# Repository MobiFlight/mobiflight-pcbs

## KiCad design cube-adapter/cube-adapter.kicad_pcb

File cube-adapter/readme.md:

# MobiFlight Cube Adapter
The MobiFlight Cube Adapter is a breakout board to learn and experiment with the different input and output devices that are supported by MobiFlight.
The board uses XH JST connectors of different sizes depending on the type of device. These connectors ensure a secure connection and correct orientation of the plugs.

## Devices overview

### Button 1 - 6
Simple buttons that connect with just two wires.

Left pin is Ground, right pin is VCC.

### LEDs 1 - 6
All LEDs are using PWM enabled pins and can be dimmed in MobiFlight.
It is recommended to add a apropriate resistor for you LED. 
More information: https://github.com/MobiFlight/MobiFlight-Connector/wiki/Input-and-Output-devices#led--output

Left pin is Ground, right pin is VCC.

### Switch 1 - 5 (On-On)
Connector is designed for On-On switches or two position switches.
More information: https://github.com/MobiFlight/MobiFlight-Connector/wiki/Input-and-Output-devices#buttons-and-switches

Left pin is Button 1, middle pin is GND, right pin is Button 2.

### Switch 6 - 10 (On-Off-On)
Connector is designed for On-Off-On switches or three position switches.
More information: https://github.com/MobiFlight/MobiFlight-Connector/wiki/Input-and-Output-devices#buttons-and-switches

* Left pin is Button 1,
* middle pin is GND, 
* right pin is Button 2.

### 7-Segment 1
Connect a 7219MAX-chip based board to this pin.
More information: https://github.com/MobiFlight/MobiFlight-Connector/wiki/Input-and-Output-devices#7-segment-modules

* 1st pin GND,
* 2nd pin VCC,
* 3rd pin DIN,
* 4th pin CS,
* 5th pin CLK

### Encoder 1-3
Connect a Encoder with Push Button function.
More information: https://github.com/MobiFlight/MobiFlight-Connector/wiki/Input-and-Output-devices#encoders

* 1st pin GND
* 2nd pin Left Pin (A)
* 3rd pin Right Pin (B)
* 4th pin Push Button

### Pot 1 - 3
Connect a Potentiometer or other analog input device.
More information: https://github.com/MobiFlight/MobiFlight-Connector/wiki/Input-and-Output-devices#analog-inputs

* 1st pin GND
* 2nd pin Reading
* 3rd pin VCC

### Shift-Register 1-2
Connect an output shift register.
More information: https://github.com/MobiFlight/MobiFlight-Connector/wiki/Input-and-Output-devices#output-shift-registers

* 1st pin GND
* 2nd pin VCC
* 3rd pin SPI (Latch)
* 4th pin SPI (Clock)
* 5th pin SPI (Data)

### Servo 1-2
Connect a servo. More information: https://github.com/MobiFlight/MobiFlight-Connector/wiki/Input-and-Output-devices#servos-motors

### Stepper 1-2
Connect a stepper. More information: https://github.com/MobiFlight/MobiFlight-Connector/wiki/Input-and-Output-devices#stepper-motors

### LCD Display 1-2
Connect a LCD Display. More information: https://github.com/MobiFlight/MobiFlight-Connector/wiki/Input-and-Output-devices#lcd-displays

* 1st pin GND
* 2nd pin VCC
* 3rd pin I2C - SDA
* 4th pin I2C - SCL

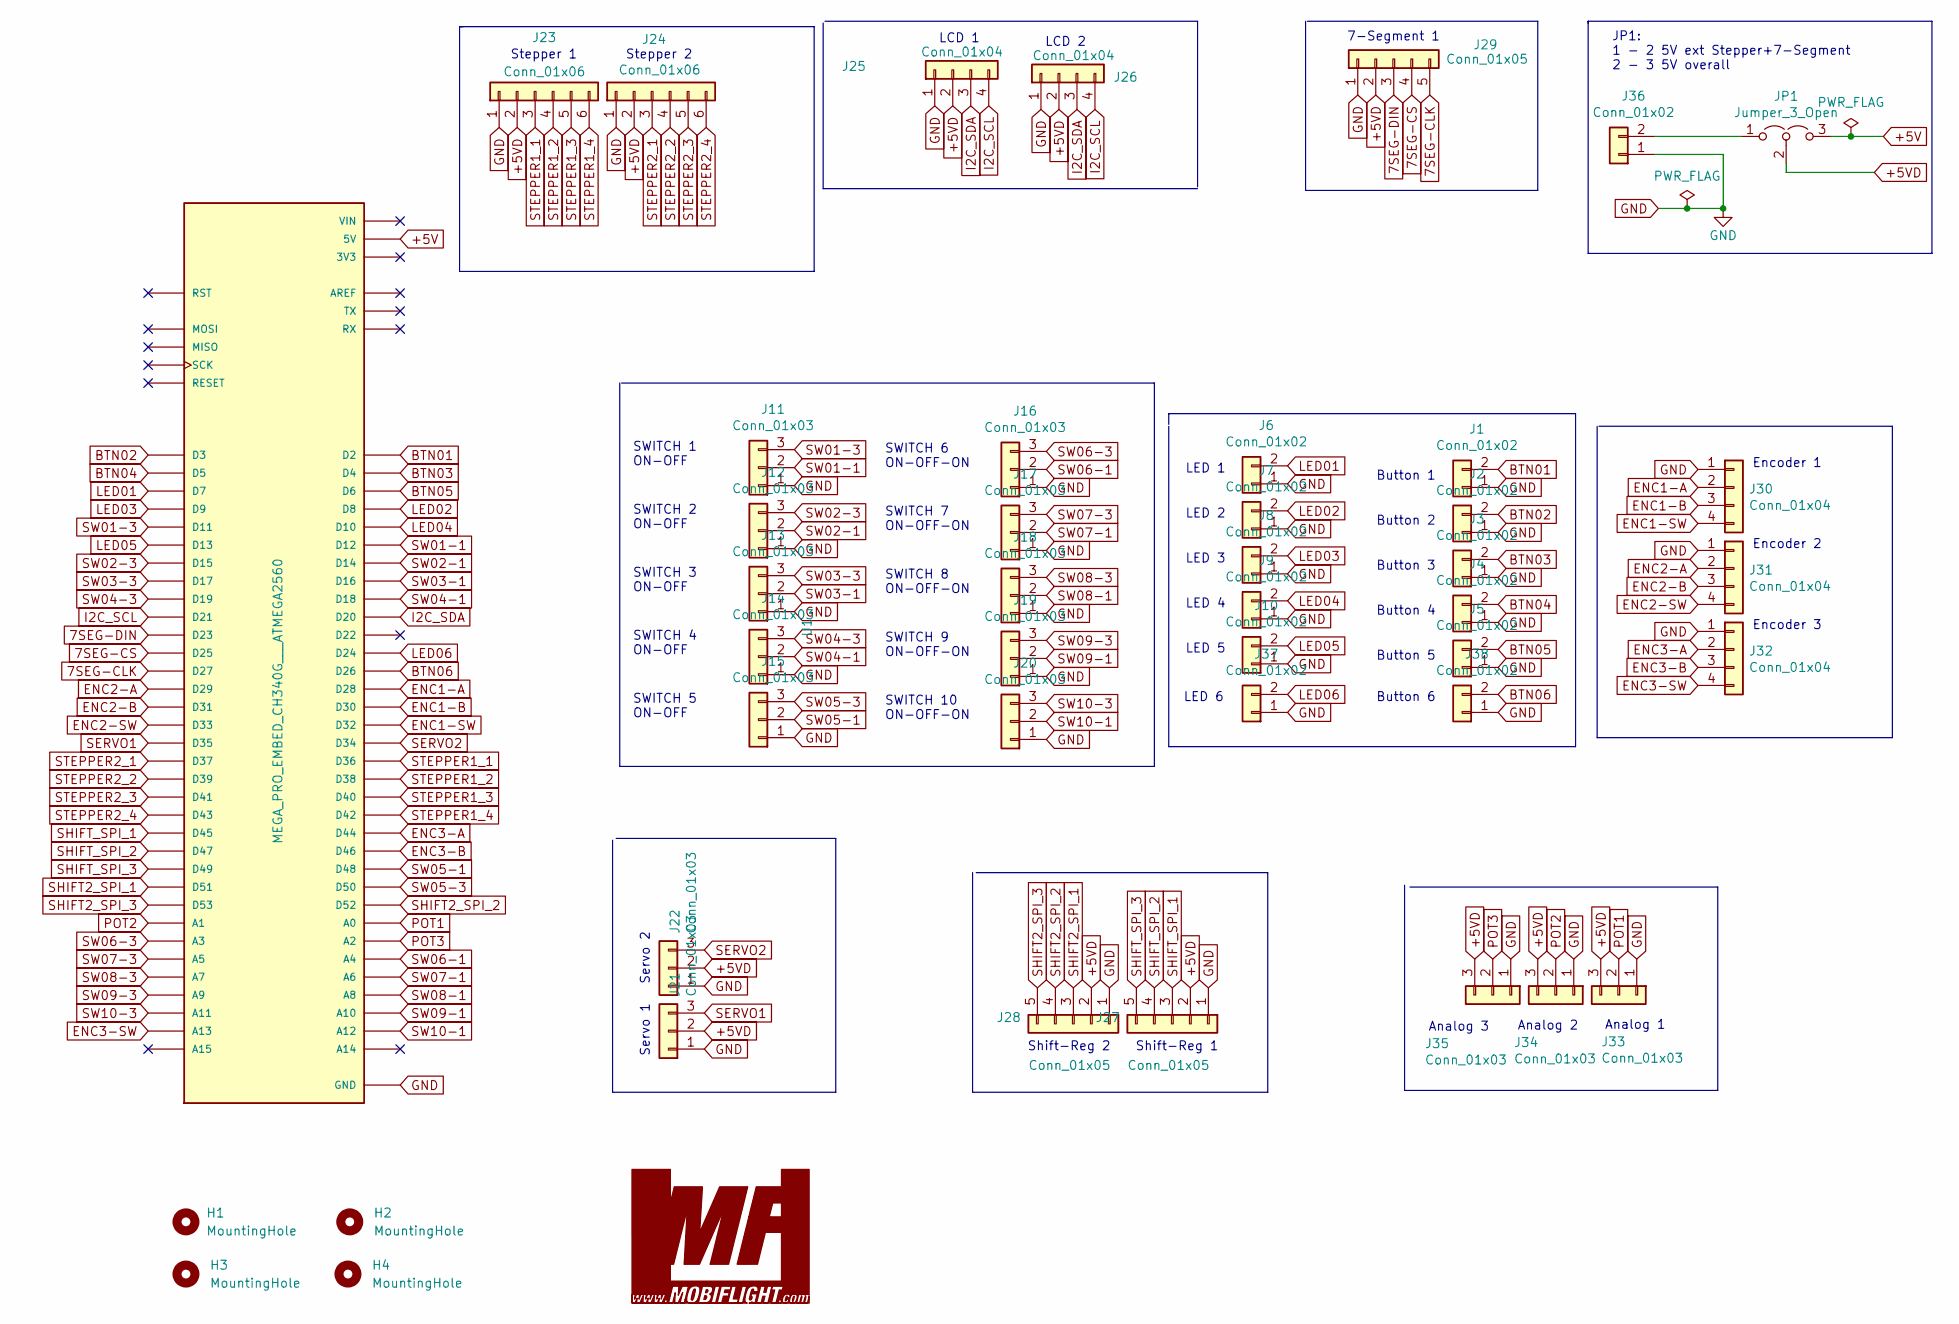
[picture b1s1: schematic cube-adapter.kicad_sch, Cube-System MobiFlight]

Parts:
H1, H2, H3, H4: MountingHole; MountingHole_3.5mm
J1, J2, J3, J4, J5, J6, J7, J8, J9, J10, J36, J37, J38: Conn_01x02; JST_XH_B2B-XH-A_1x02_P2.50mm_Vertical
J11, J12, J13, J14, J15, J16, J17, J18, J19, J20, J21, J22, J33, J34, J35: Conn_01x03; JST_XH_B3B-XH-A_1x03_P2.50mm_Vertical
J23, J24: Conn_01x06; JST_XH_B6B-XH-A_1x06_P2.50mm_Vertical
J25, J26, J30, J31, J32: Conn_01x04; JST_XH_B4B-XH-A_1x04_P2.50mm_Vertical
J27, J28, J29: Conn_01x05; JST_XH_B5B-XH-A_1x05_P2.50mm_Vertical
JP1: Jumper_3_Open; PinHeader_1x03_P2.54mm_Vertical
U1: MEGA_PRO_EMBED_CH340G___ATMEGA2560; _ATMEGA2560; PARTREV 12/May/2017

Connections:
7SEG-CLK: J29.5, U1.D27
7SEG-CS: J29.4, U1.D25
7SEG-DIN: J29.3, U1.D23
+5V: JP1.3 (B), U1.5V_1 (5V), U1.5V_2 (5V), U1.5V_3 (5V)
+5VD: J21.2, J22.2, J23.2, J24.2, J25.2, J26.2, J27.2, J28.2, J29.2, J33.3, J34.3, J35.3, JP1.2 (C)
BTN01: J1.2, U1.D2
BTN02: J2.2, U1.D3
BTN03: J3.2, U1.D4
BTN04: J4.2, U1.D5
BTN05: J5.2, U1.D6
BTN06: J38.2, U1.D26
ENC1-A: J30.2, U1.D28
ENC1-B: J30.3, U1.D30
ENC1-SW: J30.4, U1.D32
ENC2-A: J31.2, U1.D29
ENC2-B: J31.3, U1.D31
ENC2-SW: J31.4, U1.D33
ENC3-A: J32.2, U1.D44
ENC3-B: J32.3, U1.D46
ENC3-SW: J32.4, U1.A13
GND: J1.1, J2.1, J3.1, J4.1, J5.1, J6.1, J7.1, J8.1, J9.1, J10.1, J11.1, J12.1, J13.1, J14.1, J15.1, J16.1, J17.1, J18.1, J19.1, J20.1, J21.1, J22.1, J23.1, J24.1, J25.1, J26.1, J27.1, J28.1, J29.1, J30.1, J31.1, J32.1, J33.1, J34.1, J35.1, J36.1, J37.1, J38.1, U1.GND_1 (GND), U1.GND_2 (GND), U1.GND_3 (GND)
I2C_SCL: J25.4, J26.4, U1.D21
I2C_SDA: J25.3, J26.3, U1.D20
LED01: J6.2, U1.D7
LED02: J7.2, U1.D8
LED03: J8.2, U1.D9
LED04: J9.2, U1.D10
LED05: J10.2, U1.D13
LED06: J37.2, U1.D24
unnamed: J36.2, JP1.1 (A)
POT1: J33.2, U1.A0
POT2: J34.2, U1.A1
POT3: J35.2, U1.A2
SERVO1: J21.3, U1.D35
SERVO2: J22.3, U1.D34
SHIFT2_SPI_1: J28.3, U1.D51
SHIFT2_SPI_2: J28.4, U1.D52
SHIFT2_SPI_3: J28.5, U1.D53
SHIFT_SPI_1: J27.3, U1.D45
SHIFT_SPI_2: J27.4, U1.D47
SHIFT_SPI_3: J27.5, U1.D49
STEPPER1_1: J23.3, U1.D36
STEPPER1_2: J23.4, U1.D38
STEPPER1_3: J23.5, U1.D40
STEPPER1_4: J23.6, U1.D42
STEPPER2_1: J24.3, U1.D37
STEPPER2_2: J24.4, U1.D39
STEPPER2_3: J24.5, U1.D41
STEPPER2_4: J24.6, U1.D43
SW01-1: J11.2, U1.D12
SW01-3: J11.3, U1.D11
SW02-1: J12.2, U1.D14
SW02-3: J12.3, U1.D15
SW03-1: J13.2, U1.D16
SW03-3: J13.3, U1.D17
SW04-1: J14.2, U1.D18
SW04-3: J14.3, U1.D19
SW05-1: J15.2, U1.D48
SW05-3: J15.3, U1.D50
SW06-1: J16.2, U1.A4
SW06-3: J16.3, U1.A3
SW07-1: J17.2, U1.A6
SW07-3: J17.3, U1.A5
SW08-1: J18.2, U1.A8
SW08-3: J18.3, U1.A7
SW09-1: J19.2, U1.A10
SW09-3: J19.3, U1.A9
SW10-1: J20.2, U1.A12
SW10-3: J20.3, U1.A11

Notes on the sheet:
SWITCH 6 ON-OFF-ON
Button 6
Servo 1
Analog 3
LCD 2
LED 5
Shift-Reg 1
LED 4
SWITCH 4 ON-OFF
Encoder 3
Button 1
Analog 1
JP1: 1 - 2 5V ext Stepper+7-Segment 2 - 3 5V overall
SWITCH 9 ON-OFF-ON
7-Segment 1
Encoder 2
SWITCH 3 ON-OFF
Analog 2
Servo 2
Encoder 1
SWITCH 8 ON-OFF-ON
LED 1
Stepper 1
Button 3
SWITCH 2 ON-OFF
LED 2
SWITCH 10 ON-OFF-ON
Shift-Reg 2
LED 3
SWITCH 1 ON-OFF
LED 6
Button 5
Button 2
SWITCH 5 ON-OFF
Button 4
LCD 1
Stepper 2
SWITCH 7 ON-OFF-ON

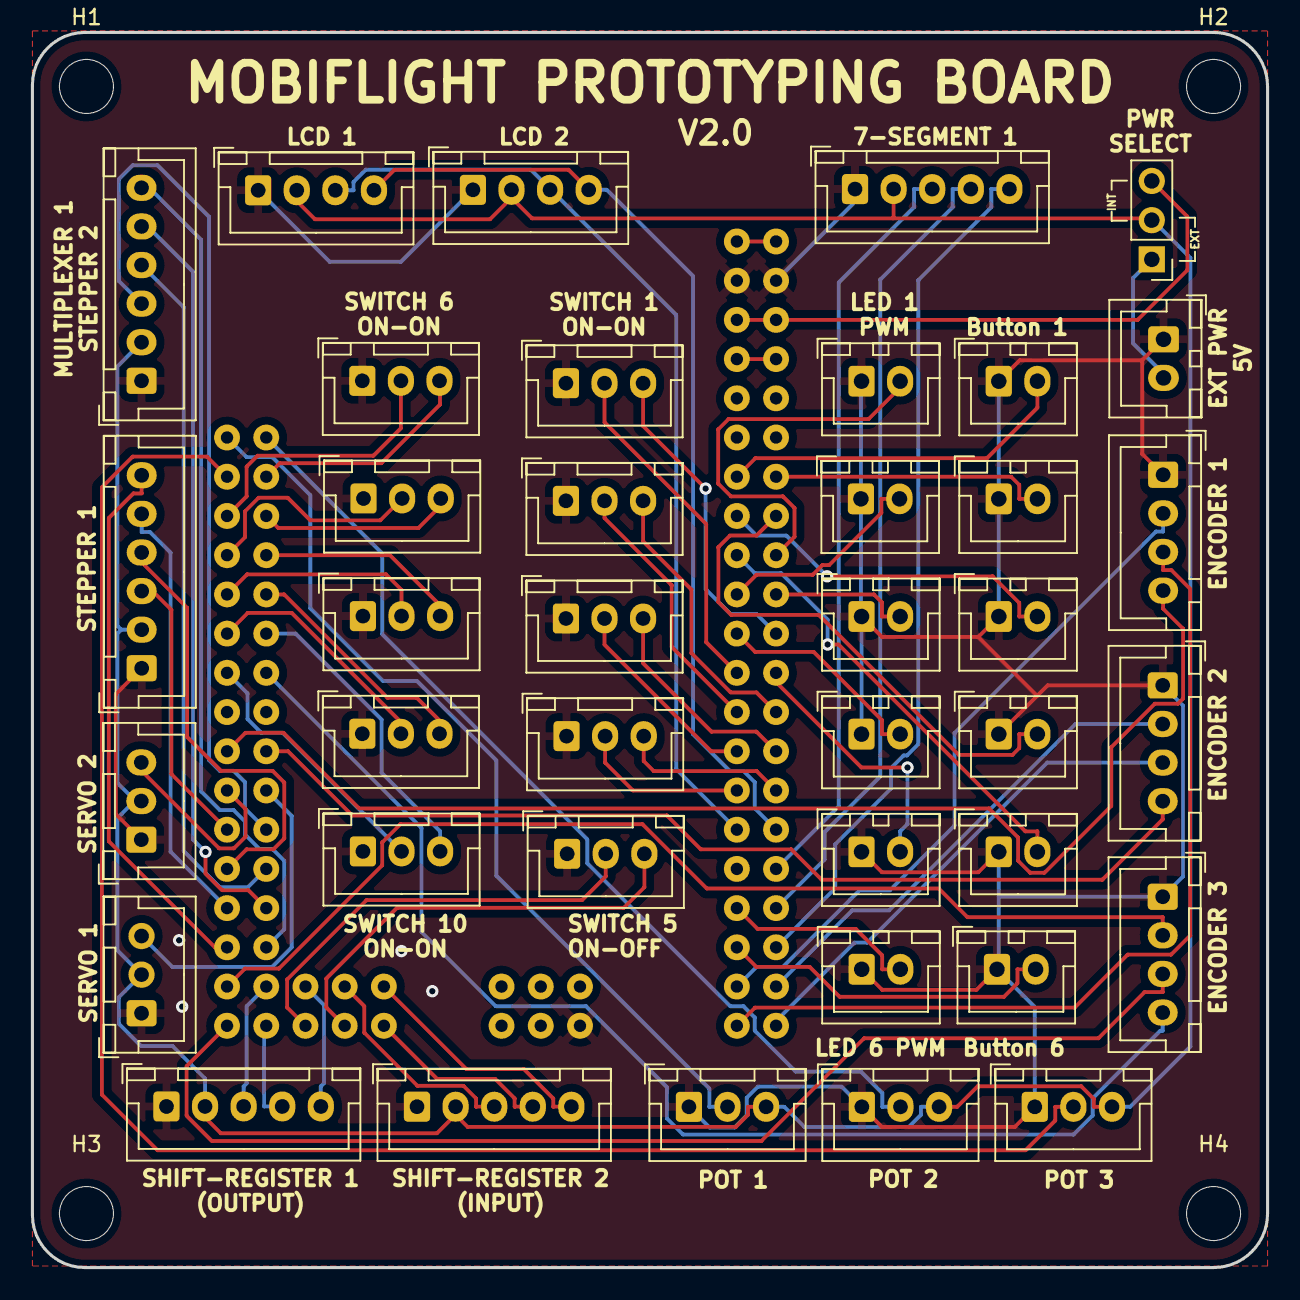
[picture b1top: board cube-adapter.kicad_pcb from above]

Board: 2 copper layers, 80.0 x 80.0 mm, 44 parts (1 on the bottom side), 69 nets.

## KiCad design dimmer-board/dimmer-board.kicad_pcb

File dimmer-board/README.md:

# Light dimmer board

This is a light dimmer board for backlight and cockpit lights, works as a shield on a full sized Arduino Mega, or standalone.

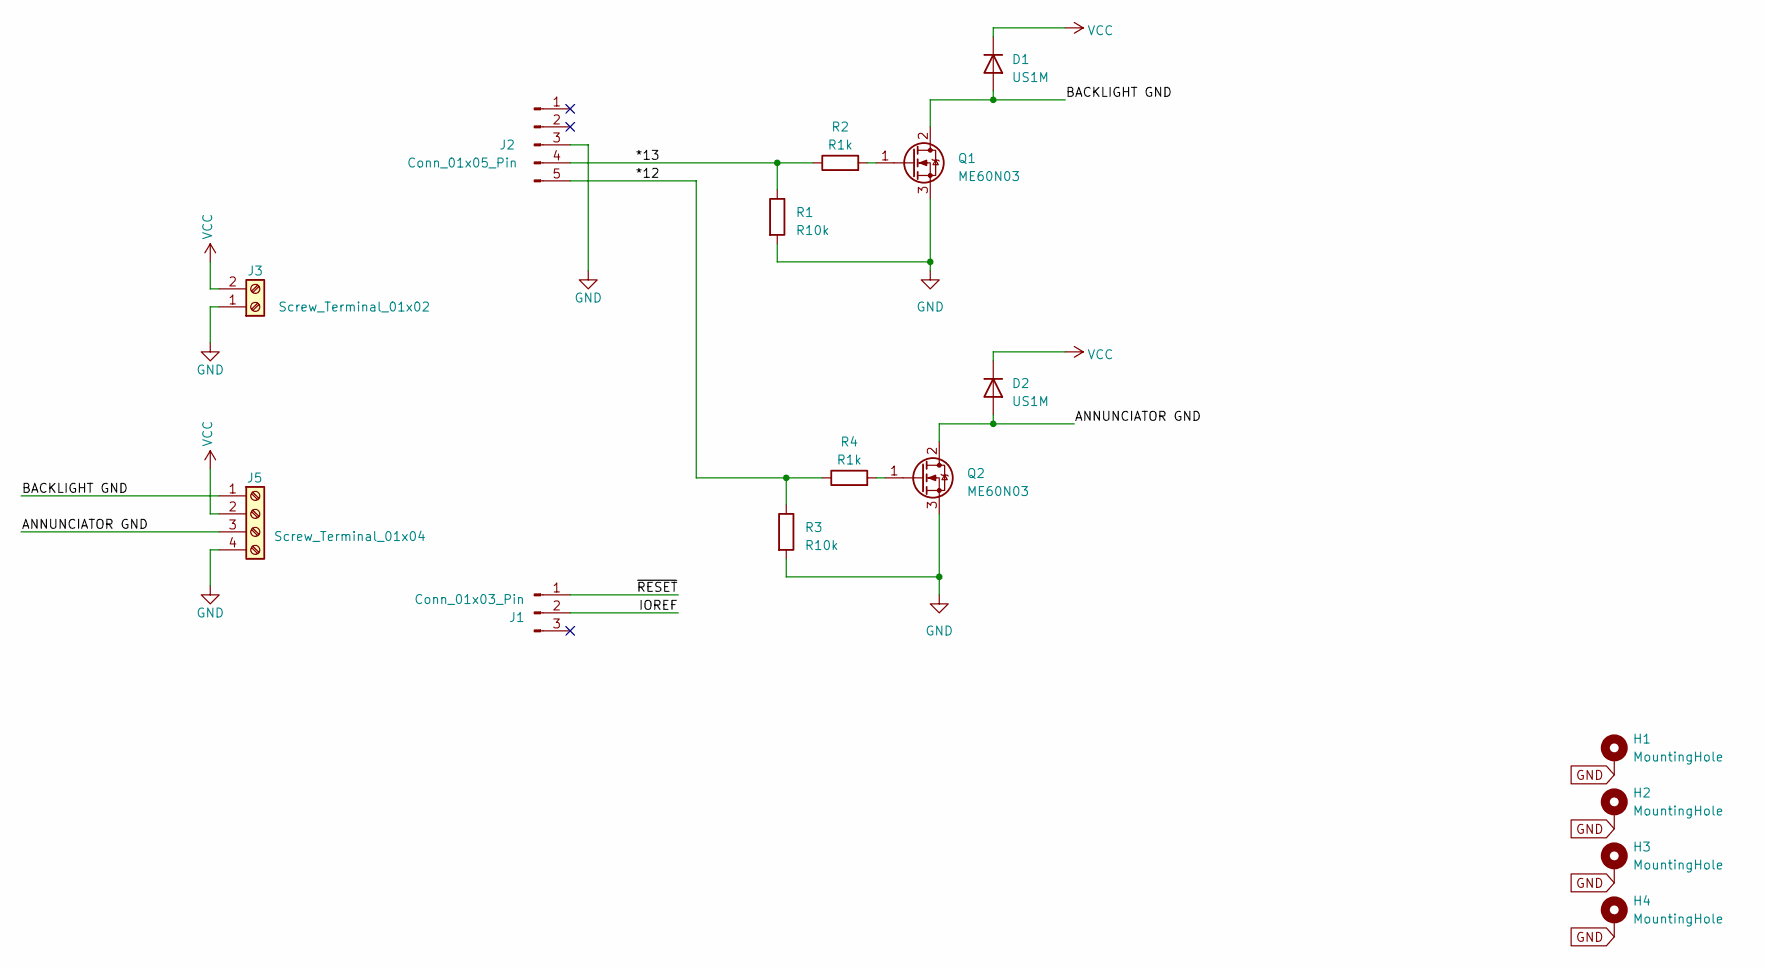
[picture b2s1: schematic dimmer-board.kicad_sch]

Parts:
D1, D2: US1M; D_SMA; LCSC C412437
H1, H2, H3, H4: MountingHole; MountingHole_3.2mm_M3_ISO14580_Pad_TopBottom
J1: Conn_01x03_Pin; PinHeader_1x03_P2.54mm_Vertical
J2: Conn_01x05_Pin; PinHeader_1x05_P2.54mm_Vertical
J3: Screw_Terminal_01x02; TerminalBlock_bornier-2_P5.08mm; LCSC C395882
J5: Screw_Terminal_01x04; TerminalBlock_bornier-4_P5.08mm; LCSC C3034542
Q1, Q2: ME60N03; TO-252-2; LCSC C165232
R1, R3: R10k; R_1206_3216Metric; LCSC C17902
R2, R4: R1k; R_1206_3216Metric; LCSC C4410

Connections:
/*12: J2.5, R3.1, R4.1
/*13: J2.4, R1.1, R2.1
/ANNUNCIATOR GND: D2.2 (A), J5.3, Q2.2 (D)
/BACKLIGHT GND: D1.2 (A), J5.1, Q1.2 (D)
/IOREF: J1.2
/~RESET: J1.1
GND: H1.1, H2.1, H3.1, H4.1, J2.3, J3.1, J5.4, Q1.3 (S), Q2.3 (S), R1.2, R3.2
unnamed: Q1.1 (G), R2.2
unnamed: Q2.1 (G), R4.2
VCC: D1.1 (K), D2.1 (K), J3.2, J5.2

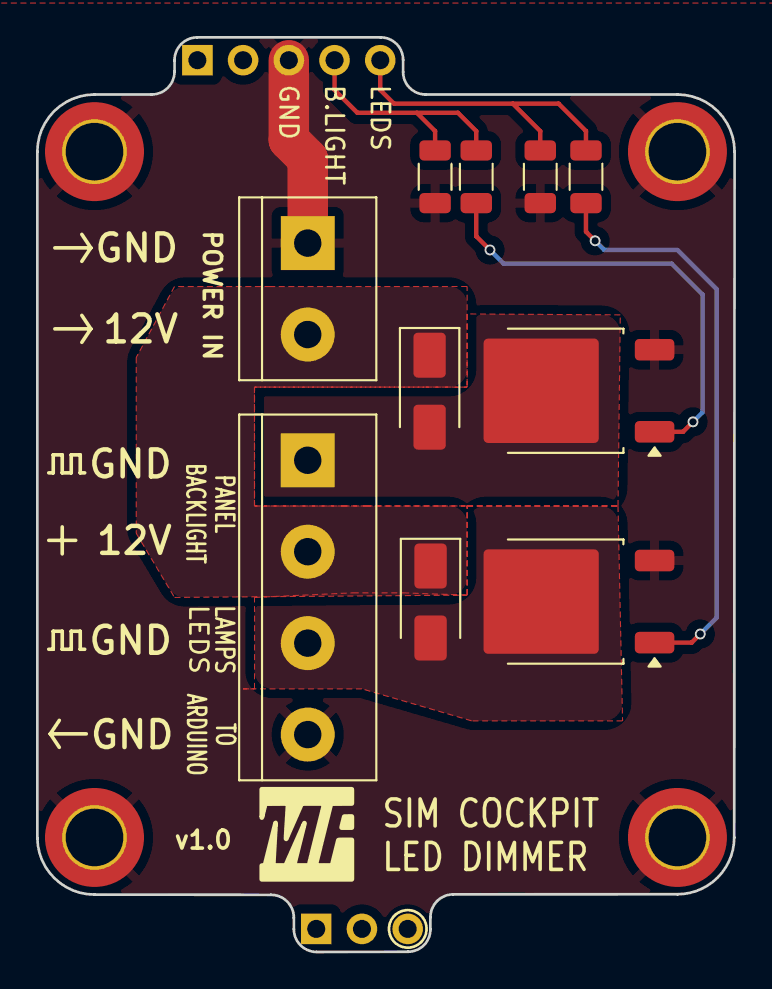
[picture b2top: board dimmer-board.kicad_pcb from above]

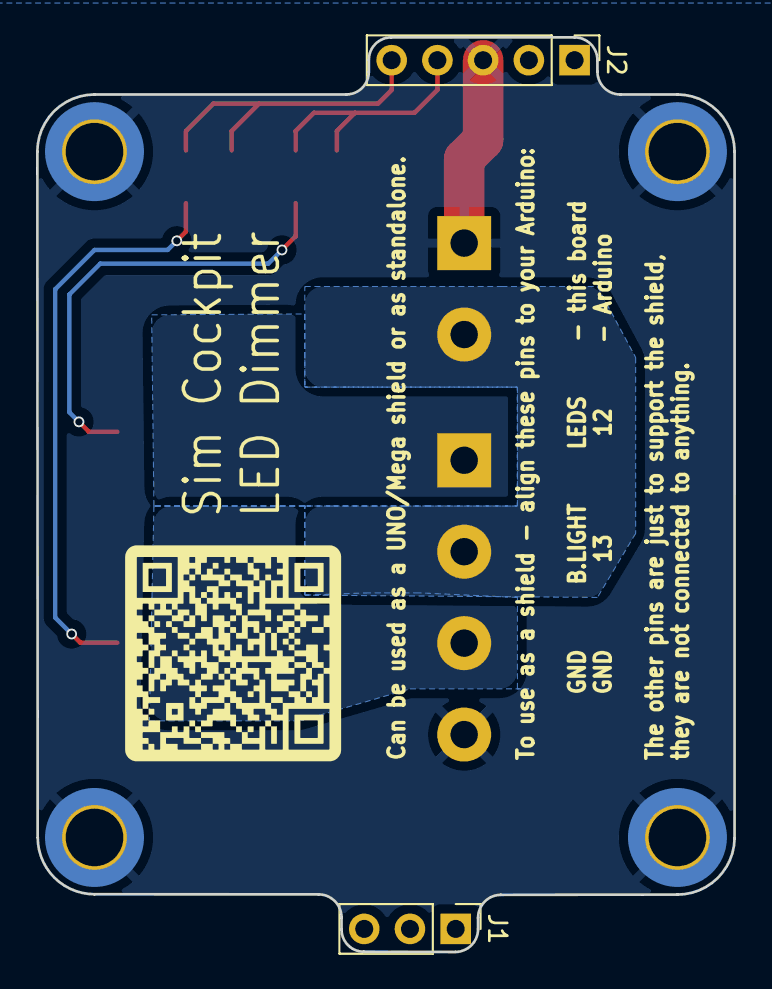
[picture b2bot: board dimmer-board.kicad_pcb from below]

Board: 2 copper layers, 38.7 x 50.8 mm, 16 parts (2 on the bottom side), 8 nets.

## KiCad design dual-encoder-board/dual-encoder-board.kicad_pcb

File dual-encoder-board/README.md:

# Dual encoder board

The dual encoder board was created because the commonly available and most affordable, and thus most popular 
dual encoder for cockpit building does not have threads on the shaft, and it is thus hard to mount on panels 
without using a printed circuit board.

The encoder board features a soldering footprint for the encoder as well as two JST XH connectors that let you
attach the encoder for example to a [MobiFlight Cube adapter](https://github.com/MobiFlight/mobiflight-pcbs/tree/main/cube-adapter) 
with a 4 pin JST XH cable.

The board has a 20x20mm pattern of M3 mounting holes, so you can use nylon standoffs and M3 machine screws to attach it
to an acrylic panel for example. The encoder body is about 7mm tall, so 8mm standoffs work great.

This repository contains the KiCad project files and also a gerber zip that can be used to manufacture the board.
But if you are interested in this board, you can also find it in the 
[MobiFlight Community Shop](https://shop.mobiflight.com/product/dual-encoder-bundle) bundled with a resin printed
knob set. I recreated the board while learning to use KiCad, so this is slightly different in how it looks,
but it will replace the older stock in the shop once that runs out. 

Both variants are functionally identical.

Designed by Tuomas Kuosmanen, November 2022

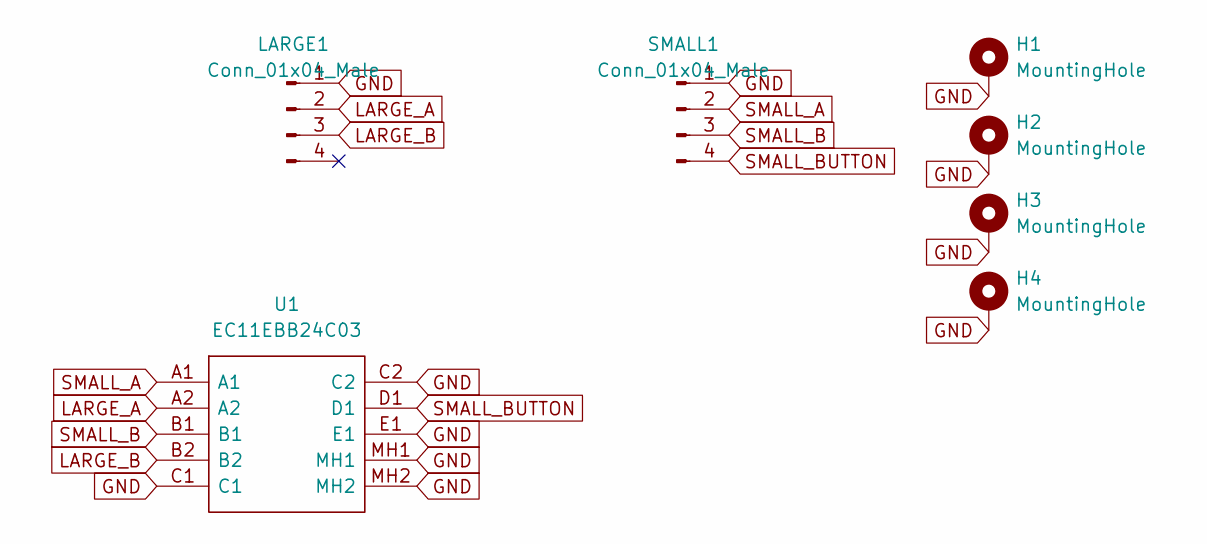
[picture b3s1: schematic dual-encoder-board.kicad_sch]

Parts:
H1, H2, H3, H4: MountingHole; MountingHole_3.2mm_M3_ISO14580_Pad_TopBottom
LARGE1: Conn_01x04_Male; JST_XH_B4B-XH-A_1x04_P2.50mm_Vertical
SMALL1: Conn_01x04_Male; JST_XH_B4B-XH-A_1x04_P2.50mm_Vertical
U1: EC11EBB24C03; EC11EBB24C03_oval; Manufacturer_Part_Number EC11EBB24C03; Mouser Part Number 688-EC11EBB24C03

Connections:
GND: H1.1, H2.1, H3.1, H4.1, LARGE1.1, SMALL1.1, U1.C1, U1.C2, U1.E1, U1.MH1, U1.MH2
LARGE_A: LARGE1.2, U1.A2
LARGE_B: LARGE1.3, U1.B2
SMALL_A: SMALL1.2, U1.A1
SMALL_B: SMALL1.3, U1.B1
SMALL_BUTTON: SMALL1.4, U1.D1

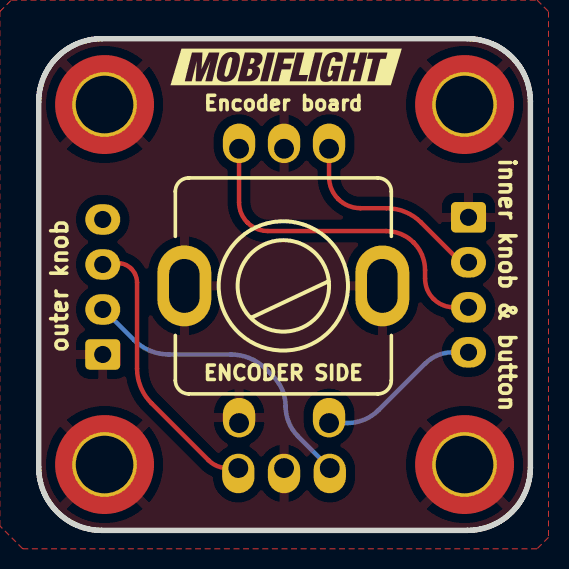
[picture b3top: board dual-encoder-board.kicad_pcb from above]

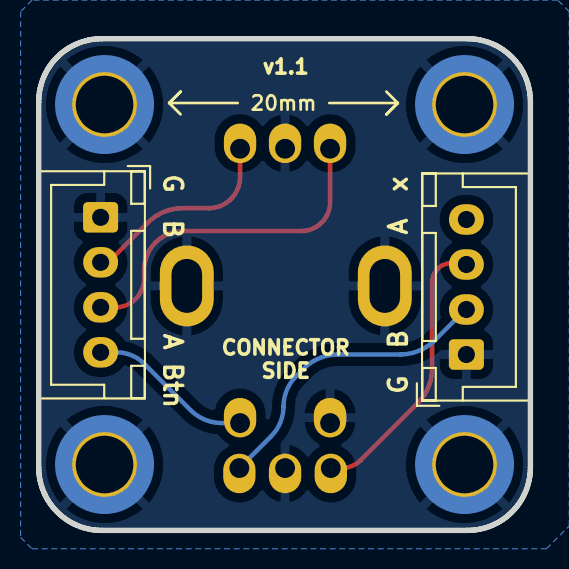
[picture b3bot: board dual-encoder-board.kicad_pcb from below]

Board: 2 copper layers, 27.3 x 27.3 mm, 8 parts (2 on the bottom side), 6 nets.

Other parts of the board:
kibuzzard-6380ACF0: G***; kibuzzard-6380ACF0

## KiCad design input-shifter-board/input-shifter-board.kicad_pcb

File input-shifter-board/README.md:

# MobiFlight Input Shifter Board
The MobiFlight Input Shifter Board is a breakout board for easier use of up to 32 buttons. It is designed to work best together with the [MobiFlight Prototyping Board](https://shop.mobiflight.com/product/prototyping-board-v2).

The board uses XH JST connectors for the individual buttons and for connecting to the Prototyping Board. Four 8 bit input shift register are daisy chained. Each input has a LED beside the connector which indicates if the button is pressed.

For more information on how to configure the board with MobiFlight, check out the [MobiFlight Connector documentation](https://docs.mobiflight.com/devices/input-shift-register/).

## Board overview

### Input Shifter IN
Connection coming from your Mobiflight board.

* Pin1 - GND
* Pin2 - VCC
* Pin3 - Latch
* Pin4 - Clock
* Pin5 - Data

### Button 1-32
Connect your button to these connectors.

Polarity does not matter for Buttons.

## Connecting and wiring
The Input Shifter board is designed to work best together with the [MobiFlight Prototyping Board](https://shop.mobiflight.com/product/prototyping-board-v2). Of course, you can also connect it directly to any of the supported microcontrollers.

### MobiFlight Prototyping Board
The prototyping board comes with the required cables to make connection super easy.

* **Connect the 5-pin wire** from the breakout board to the MobiFlight Prototyping Board's 5-pin connector labeled **Shift-Register 2**
* **Upload input shifter board configuration** to the MobiFlight Prototyping Board - [Download multiplexer-config (mfmc)](https://raw.githubusercontent.com/MobiFlight/mobiflight-pcbs/refs/heads/main/led-driver-board/prototyping-board.input-shifter.mfmc)

All inputs on the Input shifter will now work correctly!

### Direct connection
If you are using any of the supported microcontrollers, do the following:

#### Wiring
* Connect the first two pins on the **Data In** connector to **GND**, **5V** and the three remaining pins to free output-capable pins. For an Arduino Mega that could be, eg. D2, D3 D4 and D5. 

#### Board configuration
Add one input shifter device with the three data pins configured as follows and choose four times 8 bit.

Click "Upload config" and your device should work.

## MobiFlight Configuration

> This information will be added soon.

## Case
You can print a case for the board [using this STL file](breakout-multiplexer-case.stl) for better handling and look:

## Additional information

### Bottom side

### Schematic

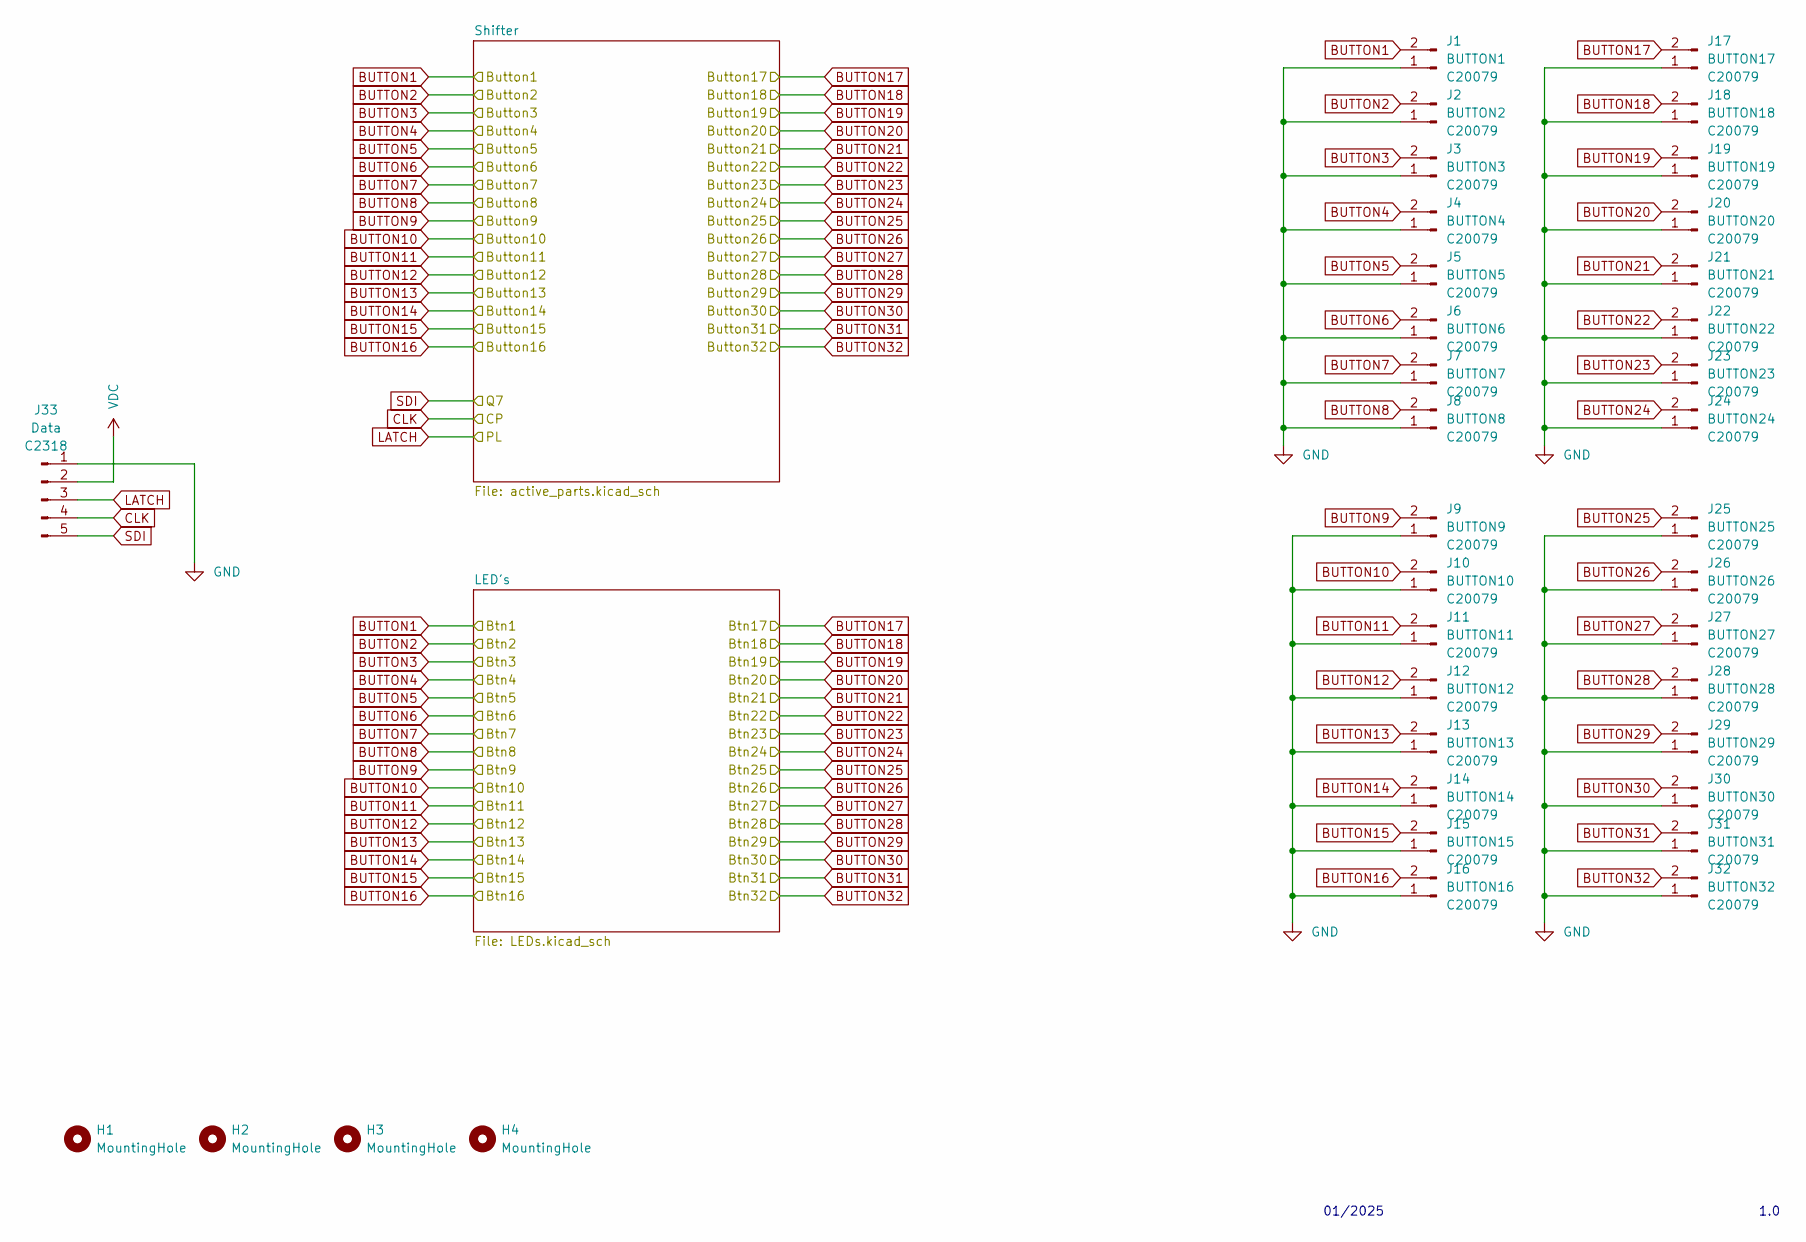
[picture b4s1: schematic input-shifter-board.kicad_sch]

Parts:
H1, H2, H3, H4: MountingHole; MountingHole_3.2mm_M3_Pad
J1: BUTTON1; JST_XH_B2B-XH-A_1x02_P2.50mm_Vertical; LCSC C20079
J2: BUTTON2; JST_XH_B2B-XH-A_1x02_P2.50mm_Vertical; LCSC C20079
J3: BUTTON3; JST_XH_B2B-XH-A_1x02_P2.50mm_Vertical; LCSC C20079
J4: BUTTON4; JST_XH_B2B-XH-A_1x02_P2.50mm_Vertical; LCSC C20079
J5: BUTTON5; JST_XH_B2B-XH-A_1x02_P2.50mm_Vertical; LCSC C20079
J6: BUTTON6; JST_XH_B2B-XH-A_1x02_P2.50mm_Vertical; LCSC C20079
J7: BUTTON7; JST_XH_B2B-XH-A_1x02_P2.50mm_Vertical; LCSC C20079
J8: BUTTON8; JST_XH_B2B-XH-A_1x02_P2.50mm_Vertical; LCSC C20079
J9: BUTTON9; JST_XH_B2B-XH-A_1x02_P2.50mm_Vertical; LCSC C20079
J10: BUTTON10; JST_XH_B2B-XH-A_1x02_P2.50mm_Vertical; LCSC C20079
J11: BUTTON11; JST_XH_B2B-XH-A_1x02_P2.50mm_Vertical; LCSC C20079
J12: BUTTON12; JST_XH_B2B-XH-A_1x02_P2.50mm_Vertical; LCSC C20079
J13: BUTTON13; JST_XH_B2B-XH-A_1x02_P2.50mm_Vertical; LCSC C20079
J14: BUTTON14; JST_XH_B2B-XH-A_1x02_P2.50mm_Vertical; LCSC C20079
J15: BUTTON15; JST_XH_B2B-XH-A_1x02_P2.50mm_Vertical; LCSC C20079
J16: BUTTON16; JST_XH_B2B-XH-A_1x02_P2.50mm_Vertical; LCSC C20079
J17: BUTTON17; JST_XH_B2B-XH-A_1x02_P2.50mm_Vertical; LCSC C20079
J18: BUTTON18; JST_XH_B2B-XH-A_1x02_P2.50mm_Vertical; LCSC C20079
J19: BUTTON19; JST_XH_B2B-XH-A_1x02_P2.50mm_Vertical; LCSC C20079
J20: BUTTON20; JST_XH_B2B-XH-A_1x02_P2.50mm_Vertical; LCSC C20079
J21: BUTTON21; JST_XH_B2B-XH-A_1x02_P2.50mm_Vertical; LCSC C20079
J22: BUTTON22; JST_XH_B2B-XH-A_1x02_P2.50mm_Vertical; LCSC C20079
J23: BUTTON23; JST_XH_B2B-XH-A_1x02_P2.50mm_Vertical; LCSC C20079
J24: BUTTON24; JST_XH_B2B-XH-A_1x02_P2.50mm_Vertical; LCSC C20079
J25: BUTTON25; JST_XH_B2B-XH-A_1x02_P2.50mm_Vertical; LCSC C20079
J26: BUTTON26; JST_XH_B2B-XH-A_1x02_P2.50mm_Vertical; LCSC C20079
J27: BUTTON27; JST_XH_B2B-XH-A_1x02_P2.50mm_Vertical; LCSC C20079
J28: BUTTON28; JST_XH_B2B-XH-A_1x02_P2.50mm_Vertical; LCSC C20079
J29: BUTTON29; JST_XH_B2B-XH-A_1x02_P2.50mm_Vertical; LCSC C20079
J30: BUTTON30; JST_XH_B2B-XH-A_1x02_P2.50mm_Vertical; LCSC C20079
J31: BUTTON31; JST_XH_B2B-XH-A_1x02_P2.50mm_Vertical; LCSC C20079
J32: BUTTON32; JST_XH_B2B-XH-A_1x02_P2.50mm_Vertical; LCSC C20079
J33: Data; JST_XH_B5B-XH-A_1x05_P2.50mm_Vertical; LCSC C2318

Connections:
BUTTON1: J1.2; also elsewhere on the board
BUTTON2: J2.2; also elsewhere on the board
BUTTON3: J3.2; also elsewhere on the board
BUTTON4: J4.2; also elsewhere on the board
BUTTON5: J5.2; also elsewhere on the board
BUTTON6: J6.2; also elsewhere on the board
BUTTON7: J7.2; also elsewhere on the board
BUTTON8: J8.2; also elsewhere on the board
BUTTON9: J9.2; also elsewhere on the board
BUTTON10: J10.2; also elsewhere on the board
BUTTON11: J11.2; also elsewhere on the board
BUTTON12: J12.2; also elsewhere on the board
BUTTON13: J13.2; also elsewhere on the board
BUTTON14: J14.2; also elsewhere on the board
BUTTON15: J15.2; also elsewhere on the board
BUTTON16: J16.2; also elsewhere on the board
BUTTON17: J17.2; also elsewhere on the board
BUTTON18: J18.2; also elsewhere on the board
BUTTON19: J19.2; also elsewhere on the board
BUTTON20: J20.2; also elsewhere on the board
BUTTON21: J21.2; also elsewhere on the board
BUTTON22: J22.2; also elsewhere on the board
BUTTON23: J23.2; also elsewhere on the board
BUTTON24: J24.2; also elsewhere on the board
BUTTON25: J25.2; also elsewhere on the board
BUTTON26: J26.2; also elsewhere on the board
BUTTON27: J27.2; also elsewhere on the board
BUTTON28: J28.2; also elsewhere on the board
BUTTON29: J29.2; also elsewhere on the board
BUTTON30: J30.2; also elsewhere on the board
BUTTON31: J31.2; also elsewhere on the board
BUTTON32: J32.2; also elsewhere on the board
CLK: J33.4; also elsewhere on the board
GND: J1.1, J2.1, J3.1, J4.1, J5.1, J6.1, J7.1, J8.1, J9.1, J10.1, J11.1, J12.1, J13.1, J14.1, J15.1, J16.1, J17.1, J18.1, J19.1, J20.1, J21.1, J22.1, J23.1, J24.1, J25.1, J26.1, J27.1, J28.1, J29.1, J30.1, J31.1, J32.1, J33.1; also elsewhere on the board
LATCH: J33.3; also elsewhere on the board
SDI: J33.5; also elsewhere on the board
VDC: J33.2; also elsewhere on the board

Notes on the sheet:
1.0
01/2025
